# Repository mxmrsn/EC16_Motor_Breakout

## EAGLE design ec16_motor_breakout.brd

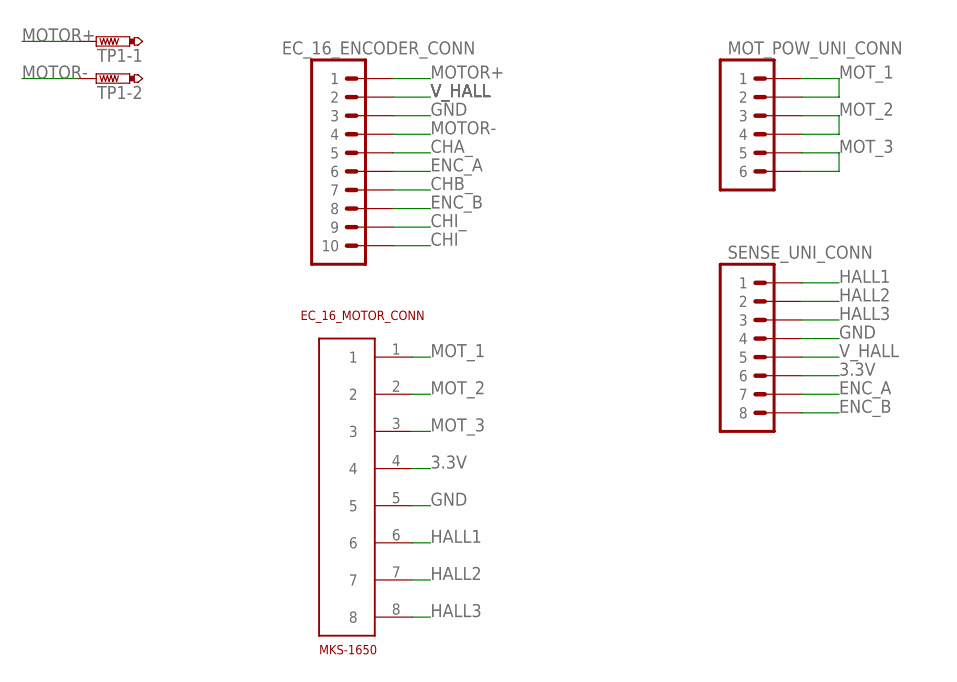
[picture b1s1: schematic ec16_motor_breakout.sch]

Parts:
EC_16_ENCODER_CONN: CONN_RECT_2X5'_VERT; 2X5
EC_16_MOTOR_CONN: MKS-1650
MOT_POW_UNI_CONN: CONN_RECT_2X3_VERT; 2X3
SENSE_UNI_CONN: CONN_RECT_2X4_; 2X4
TP1: PTR2; P2-38-17

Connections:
3.3V: EC_16_MOTOR_CONN.4, SENSE_UNI_CONN.6
CHA_: EC_16_ENCODER_CONN.5
CHB_: EC_16_ENCODER_CONN.7
CHI: EC_16_ENCODER_CONN.10
CHI_: EC_16_ENCODER_CONN.9
ENC_A: EC_16_ENCODER_CONN.6, SENSE_UNI_CONN.7
ENC_B: EC_16_ENCODER_CONN.8, SENSE_UNI_CONN.8
GND: EC_16_ENCODER_CONN.3, EC_16_MOTOR_CONN.5, SENSE_UNI_CONN.4
HALL1: EC_16_MOTOR_CONN.6, SENSE_UNI_CONN.1
HALL2: EC_16_MOTOR_CONN.7, SENSE_UNI_CONN.2
HALL3: EC_16_MOTOR_CONN.8, SENSE_UNI_CONN.3
MOTOR+: EC_16_ENCODER_CONN.1, TP1.TP-1
MOTOR-: EC_16_ENCODER_CONN.4, TP1.TP-2
MOT_1: EC_16_MOTOR_CONN.1, MOT_POW_UNI_CONN.1, MOT_POW_UNI_CONN.2
MOT_2: EC_16_MOTOR_CONN.2, MOT_POW_UNI_CONN.3, MOT_POW_UNI_CONN.4
MOT_3: EC_16_MOTOR_CONN.3, MOT_POW_UNI_CONN.5, MOT_POW_UNI_CONN.6
V_HALL: EC_16_ENCODER_CONN.2, SENSE_UNI_CONN.5

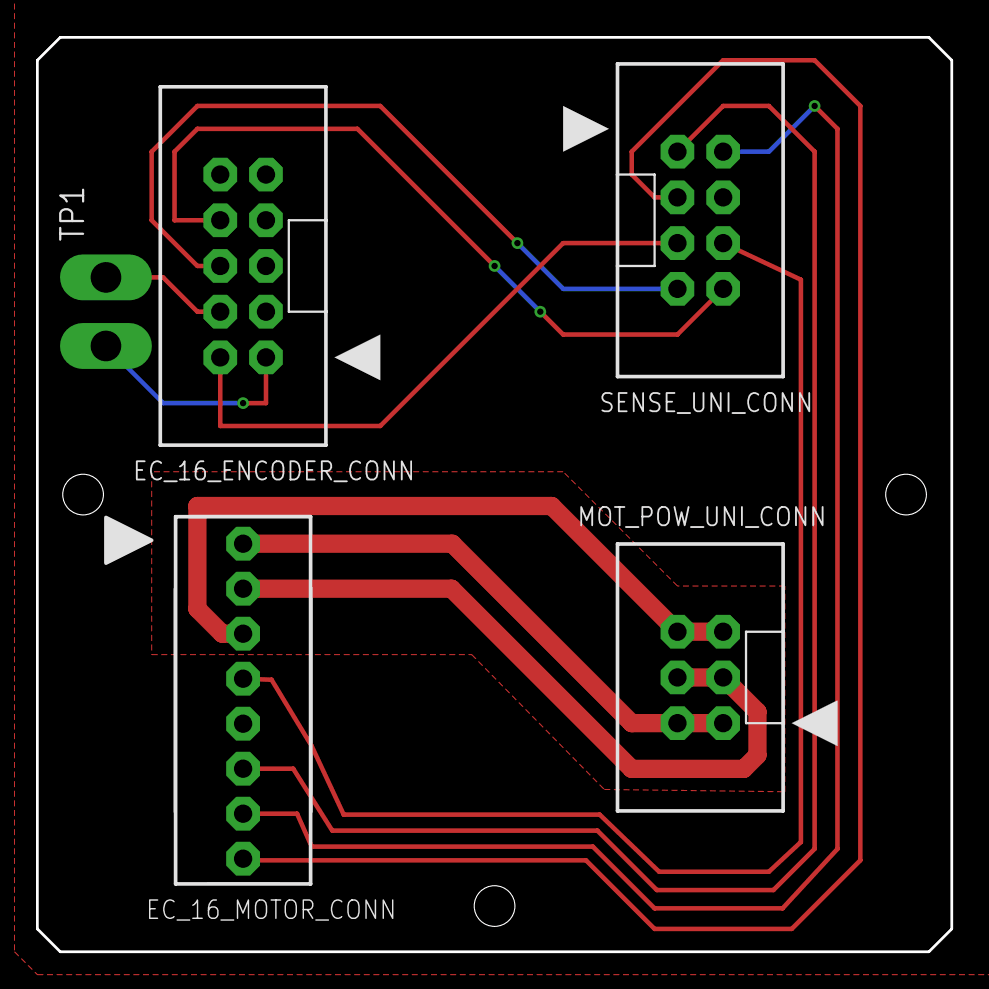
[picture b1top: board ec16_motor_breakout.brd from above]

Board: 2 copper layers, 50.8 x 50.8 mm, 5 parts (0 on the bottom side), 13 nets.

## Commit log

2023-03-11 clean up
